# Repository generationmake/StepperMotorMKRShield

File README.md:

# StepperMotorMKRShield
StepperMotorMKRShield with Trinamic TMC5130A-TA drivers for two stepper motors compatible with Arduino MKR 

## PCB

### Top

### Bottom

## License

This hardware is licensed under the CERN OHL v. 1.2

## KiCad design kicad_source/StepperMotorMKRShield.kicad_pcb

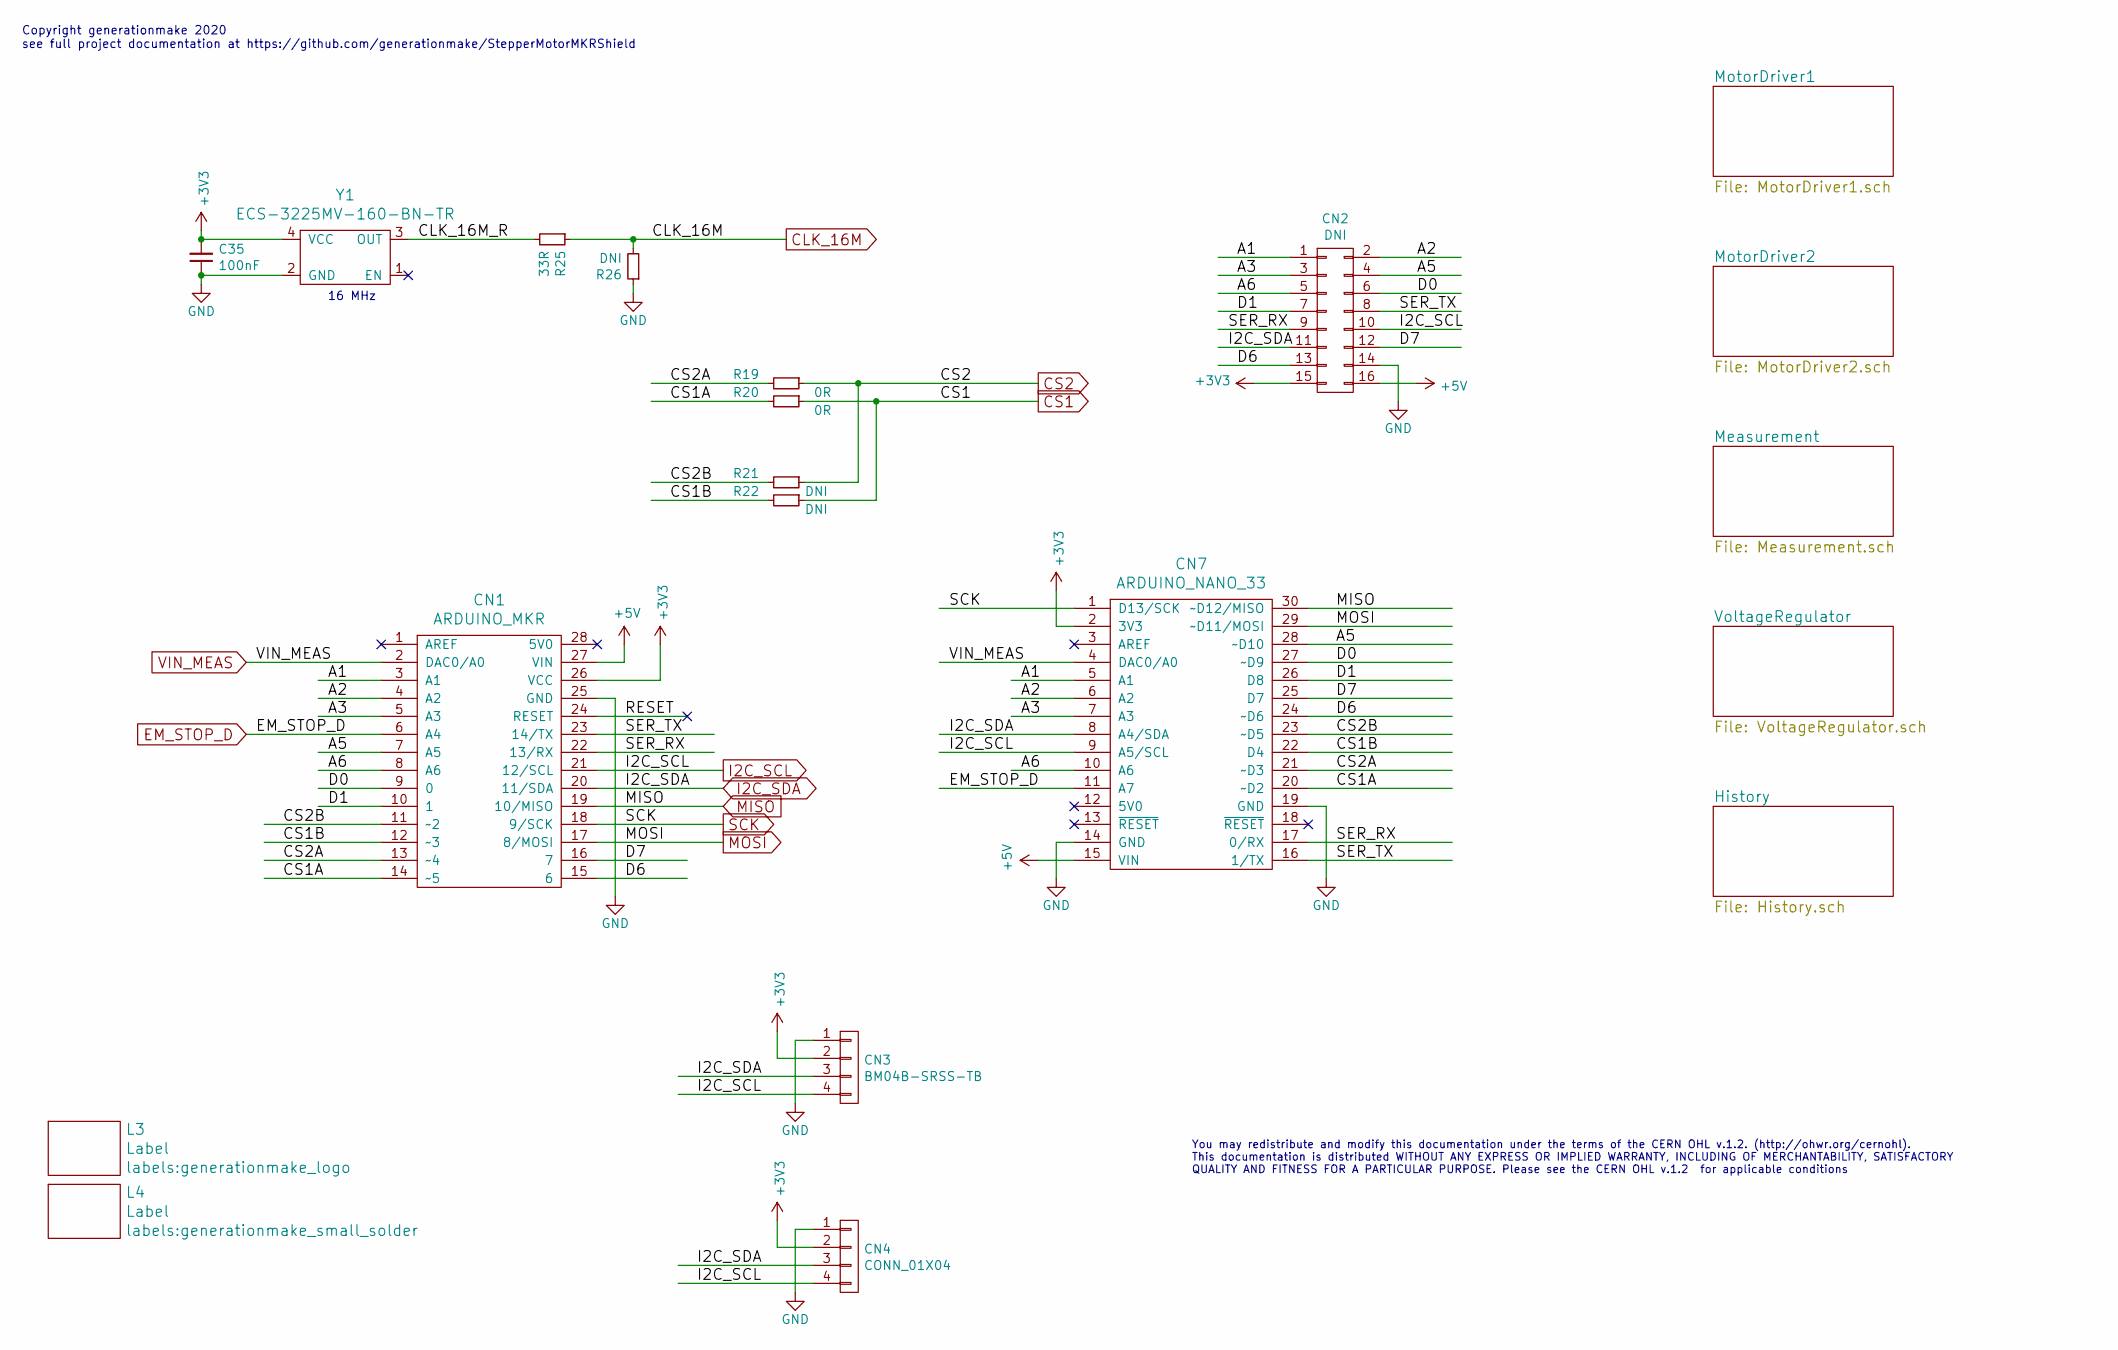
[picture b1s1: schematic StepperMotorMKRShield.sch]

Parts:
C35: 100nF; C_0603
CN1: ARDUINO_MKR; ARDUINO_MKR_BASEBOARD
CN2: DNI; Pin_Header_Straight_2x08
CN3: BM04B-SRSS-TB; Connectors_JST_BM04B-SRSS-TB
CN4: CONN_01X04; Pin_Header_Straight_1x04
CN7: ARDUINO_NANO_33
L3: Label; generationmake_logo
L4: Label; generationmake_small_solder
R19, R20: 0R; R_0603
R21, R22, R26: DNI; R_0603
R25: 33R; R_0603
Y1: ECS-3225MV-160-BN-TR; Crystal_SMD_3.2x2.5mm_4Pad

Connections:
+3V3: C35.2, CN1.26 (VCC), CN2.15, CN3.2, CN4.2, CN7.2 (3V3), Y1.4 (VCC); also elsewhere on the board
+5V: CN1.27 (VIN), CN2.16, CN7.15 (VIN); also elsewhere on the board
/A1: CN1.3 (A1), CN2.1, CN7.5 (A1)
/A2: CN1.4 (A2), CN2.2, CN7.6 (A2)
/A3: CN1.5 (A3), CN2.3, CN7.7 (A3)
/A5: CN1.7 (A5), CN2.4, CN7.28 (~~D10)
/A6: CN1.8 (A6), CN2.5, CN7.10 (A6)
/CLK_16M_R: R25.2, Y1.3 (OUT)
/CS1A: CN1.14 (~~5), CN7.20 (~~D2), R20.2
/CS1B: CN1.12 (~~3), CN7.22 (D4), R22.2
/CS2A: CN1.13 (~~4), CN7.21 (~~D3), R19.2
/CS2B: CN1.11 (~~2), CN7.23 (~~D5), R21.2
/D0: CN1.9 (0), CN2.6, CN7.27 (~~D9)
/D1: CN1.10 (1), CN2.7, CN7.26 (D8)
/D6: CN1.15 (6), CN2.13, CN7.24 (~~D6)
/D7: CN1.16 (7), CN2.12, CN7.25 (D7)
/SER_RX: CN1.22 (13/RX), CN2.9, CN7.17 (0/RX)
/SER_TX: CN1.23 (14/TX), CN2.8, CN7.16 (1/TX)
CLK_16M: R25.1, R26.2; also elsewhere on the board
CS1: R20.1, R22.1; also elsewhere on the board
CS2: R19.1, R21.1; also elsewhere on the board
EM_STOP_D: CN1.6 (A4), CN7.11 (A7); also elsewhere on the board
GND: C35.1, CN1.25 (GND), CN2.14, CN3.1, CN4.1, CN7.14 (GND), CN7.19 (GND), R26.1, Y1.2 (GND); also elsewhere on the board
I2C_SCL: CN1.21 (12/SCL), CN2.10, CN3.4, CN4.4, CN7.9 (A5/SCL); also elsewhere on the board
I2C_SDA: CN1.20 (11/SDA), CN2.11, CN3.3, CN4.3, CN7.8 (A4/SDA); also elsewhere on the board
MISO: CN1.19 (10/MISO), CN7.30 (~~D12/MISO); also elsewhere on the board
MOSI: CN1.17 (8/MOSI), CN7.29 (~~D11/MOSI); also elsewhere on the board
SCK: CN1.18 (9/SCK), CN7.1 (D13/SCK); also elsewhere on the board
VIN_MEAS: CN1.2 (DAC0/A0), CN7.4 (DAC0/A0); also elsewhere on the board

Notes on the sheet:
Copyright generationmake 2020 see full project documentation at https://github.com/generationmake/StepperMotorMKRShield
You may redistribute and modify this documentation under the terms of the CERN OHL v.1.2. (http://ohwr.org/cernohl). This documentation is distributed WITHOUT ANY EXPRESS OR IMPLIED WARRANTY, INCLUDING OF MERCHANTABILITY, SATISFACTORY QUALITY AND FITNESS FOR A PARTICULAR PURPOSE. Please see the CER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
16 MHz

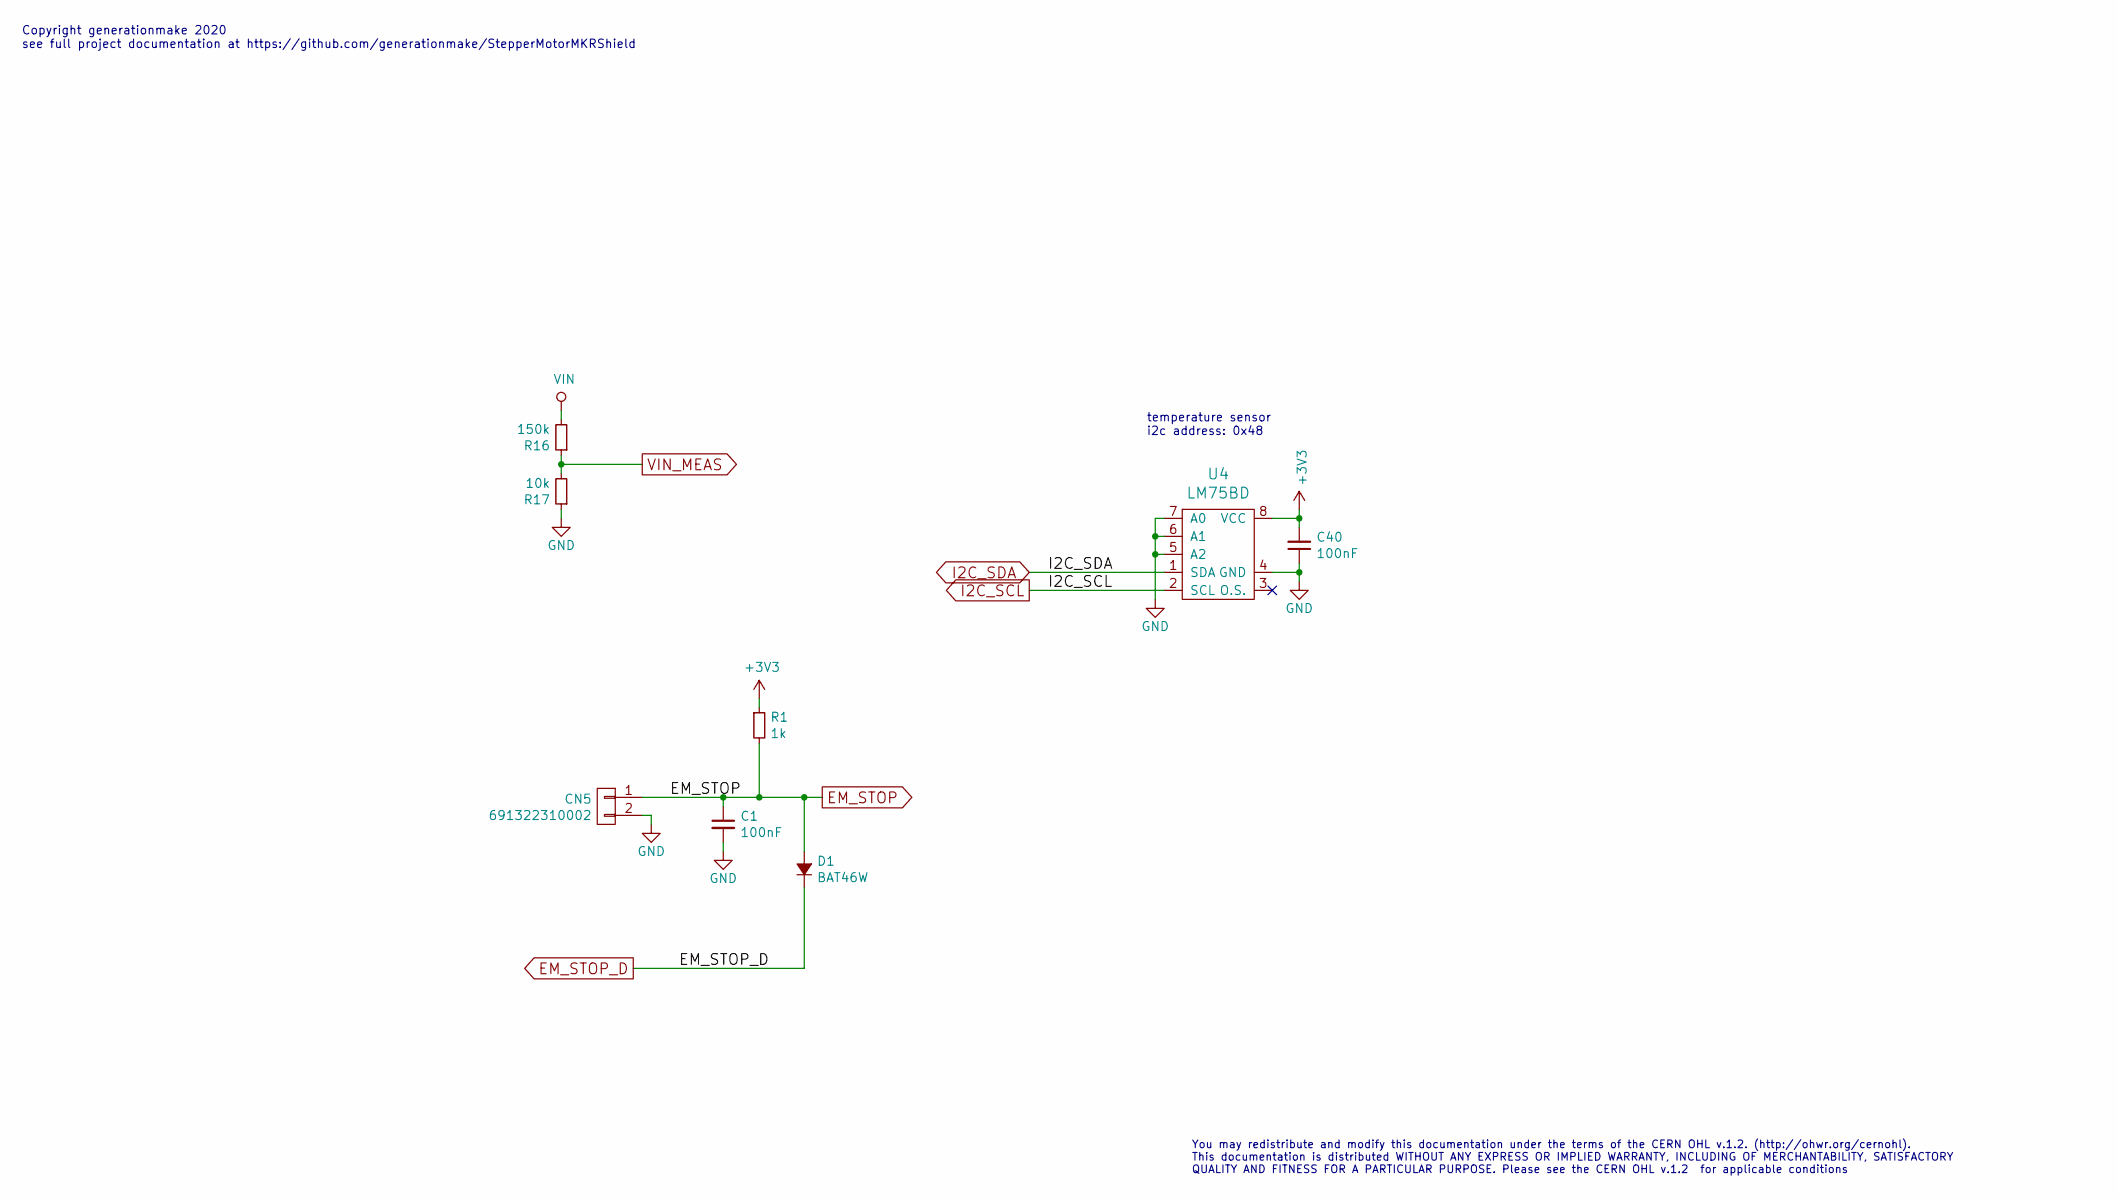
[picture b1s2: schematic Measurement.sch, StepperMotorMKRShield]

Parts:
C1, C40: 100nF; C_0603
CN5: 691322310002; WR-TBL_691322310002
D1: BAT46W; SOD-123
R1: 1k; R_0603
R16: 150k; R_0603
R17: 10k; R_0603
U4: LM75BD; SOIC-8_3.9x4.9mm_Pitch1.27mm

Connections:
+3V3: C40.2, R1.1, U4.8 (VCC); also elsewhere on the board
EM_STOP: C1.1, CN5.1, D1.2 (A), R1.2; also elsewhere on the board
EM_STOP_D: D1.1 (K); also elsewhere on the board
GND: C1.2, C40.1, CN5.2, R17.1, U4.4 (GND), U4.5 (A2), U4.6 (A1), U4.7 (A0); also elsewhere on the board
I2C_SCL: U4.2 (SCL); also elsewhere on the board
I2C_SDA: U4.1 (SDA); also elsewhere on the board
VIN: R16.2; also elsewhere on the board
VIN_MEAS: R16.1, R17.2; also elsewhere on the board

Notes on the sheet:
Copyright generationmake 2020 see full project documentation at https://github.com/generationmake/StepperMotorMKRShield
You may redistribute and modify this documentation under the terms of the CERN OHL v.1.2. (http://ohwr.org/cernohl). This documentation is distributed WITHOUT ANY EXPRESS OR IMPLIED WARRANTY, INCLUDING OF MERCHANTABILITY, SATISFACTORY QUALITY AND FITNESS FOR A PARTICULAR PURPOSE. Please see the CER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
temperature sensor i2c address: 0x48

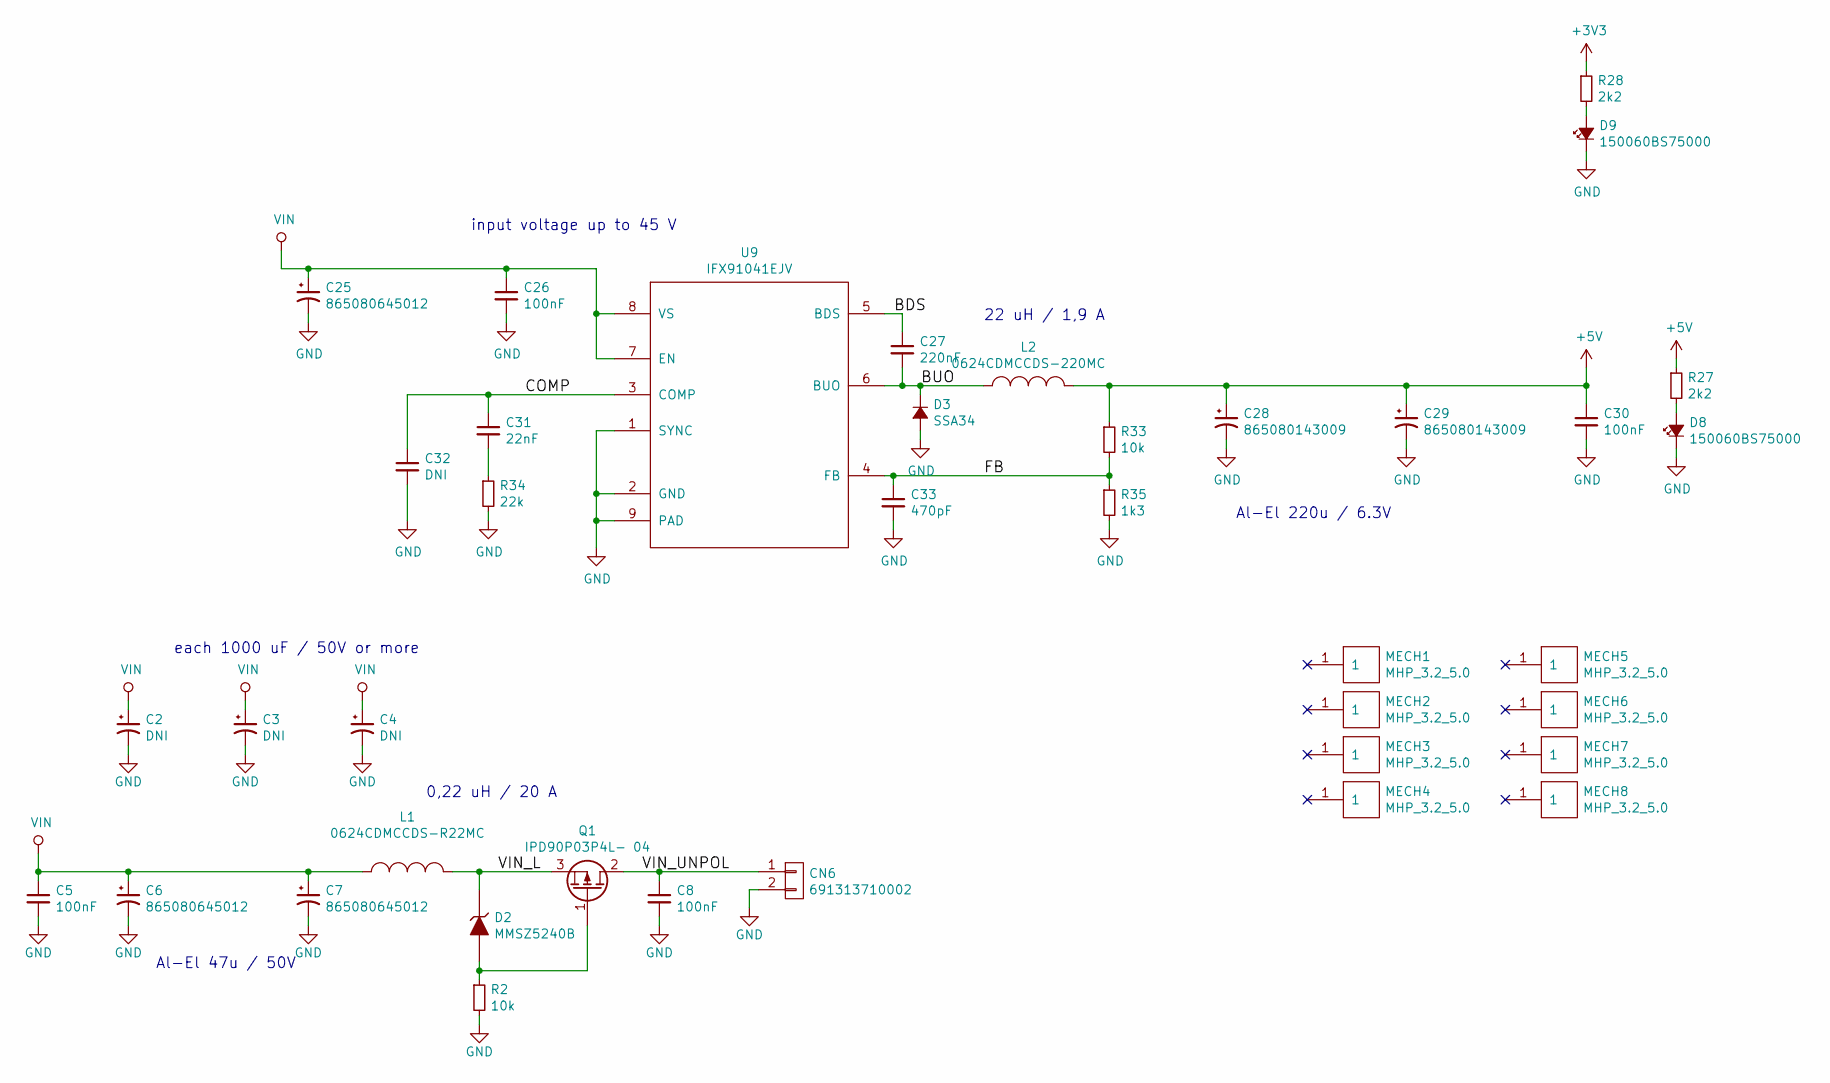
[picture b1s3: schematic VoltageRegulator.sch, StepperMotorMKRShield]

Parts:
C2, C3, C4: DNI; C_elec_THT_16x25_RM7.5
C5, C8, C26, C30: 100nF; C_0603
C6, C7, C25: 865080645012; c_elec_6.3x7.7
C27: 220nF; C_0603
C28, C29: 865080143009; c_elec_6.3x5.7
C31: 22nF; C_0603
C32: DNI; C_0603
C33: 470pF; C_0603
CN6: 691313710002; WR-TBL_691313710002
D2: MMSZ5240B; SOD-123
D3: SSA34; SMA_Standard
D8, D9: 150060BS75000; LED_0603
L1: 0624CDMCCDS-R22MC; Sumida-0624CDMCCDS
L2: 0624CDMCCDS-220MC; Sumida-0624CDMCCDS
MECH1, MECH2, MECH3, MECH4, MECH5, MECH6, MECH7, MECH8: MHP_3.2_5.0
Q1: IPD90P03P4L- 04; TO-252-2Lead
R2, R33: 10k; R_0603
R27, R28: 2k2; R_0603
R34: 22k; R_0603
R35: 1k3; R_0603
U9: IFX91041EJV; SOIC-8-1EP_3.9x4.9mm_Pitch1.27mm

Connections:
+3V3: R28.1; also elsewhere on the board
+5V: C28.1, C29.1, C30.1, L2.2, R27.1, R33.1; also elsewhere on the board
/VoltageRegulator/BDS: C27.1, U9.5 (BDS)
/VoltageRegulator/BUO: C27.2, D3.1 (K), L2.1, U9.6 (BUO)
/VoltageRegulator/COMP: C31.1, C32.1, U9.3 (COMP)
/VoltageRegulator/FB: C33.1, R33.2, R35.1, U9.4 (FB)
/VoltageRegulator/VIN_L: D2.1 (K), L1.2, Q1.3 (S)
/VoltageRegulator/VIN_UNPOL: C8.1, CN6.1, Q1.2 (D)
GND: C2.2, C3.2, C4.2, C5.2, C6.2, C7.2, C8.2, C25.2, C26.2, C28.2, C29.2, C30.2, C32.2, C33.2, CN6.2, D3.2 (A), D8.1 (K), D9.1 (K), R2.2, R34.2, R35.2, U9.1 (SYNC), U9.2 (GND), U9.9 (PAD); also elsewhere on the board
unnamed: C31.2, R34.1
unnamed: D2.2 (A), Q1.1 (G), R2.1
unnamed: D8.2 (A), R27.2
unnamed: D9.2 (A), R28.2
VIN: C2.1, C3.1, C4.1, C5.1, C6.1, C7.1, C25.1, C26.1, L1.1, U9.7 (EN), U9.8 (VS); also elsewhere on the board

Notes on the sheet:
input voltage up to 45 V
0,22 uH / 20 A
22 uH / 1,9 A
each 1000 uF / 50V or more
Al-El 47u / 50V
Al-El 220u / 6.3V

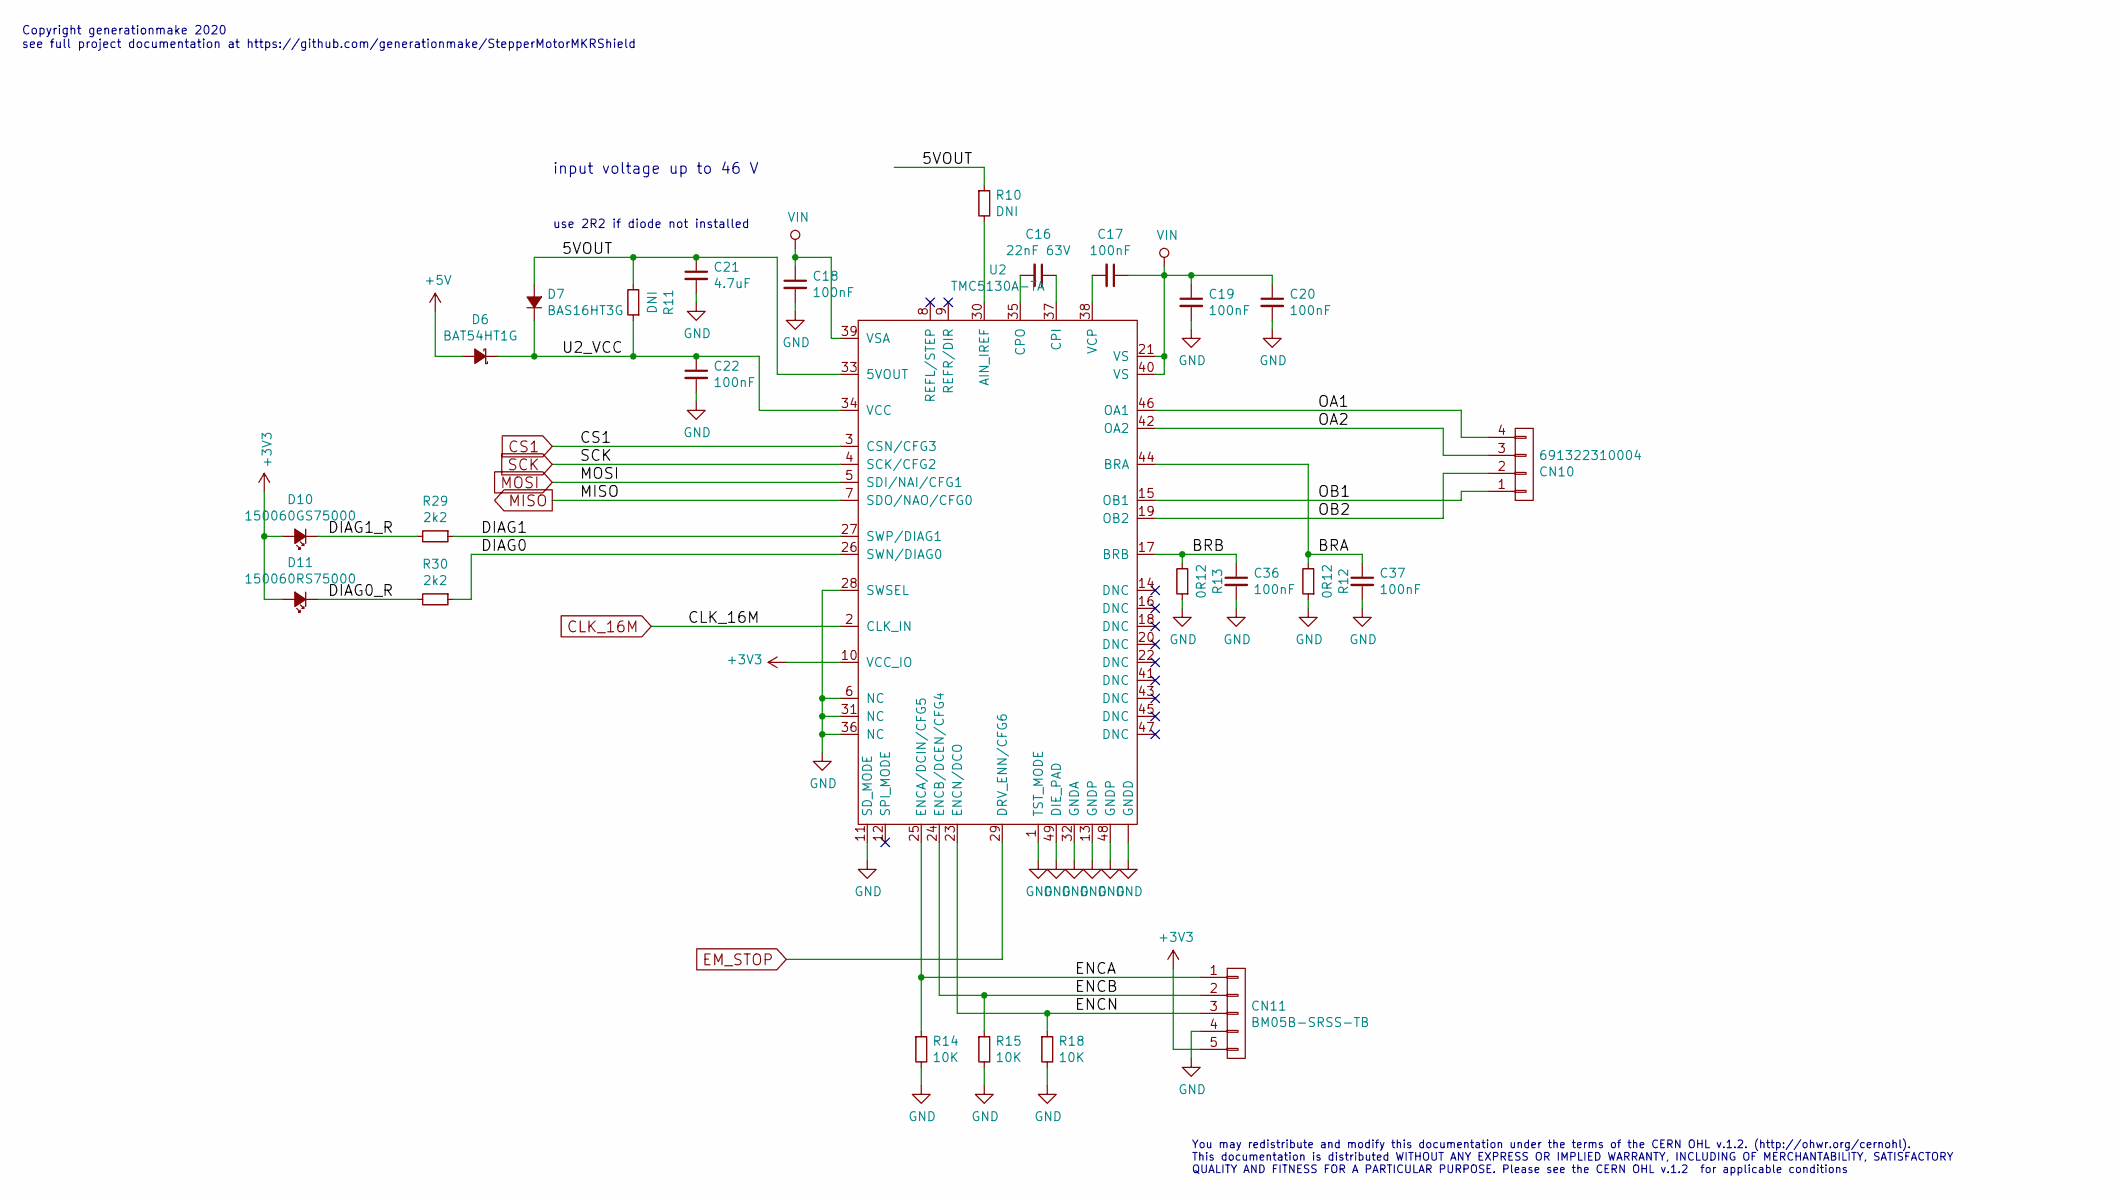
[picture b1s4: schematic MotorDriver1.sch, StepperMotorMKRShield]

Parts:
C16: 22nF 63V; C_0603
C17, C18, C19, C20, C22, C36, C37: 100nF; C_0603
C21: 4.7uF; C_0603
CN10: 691322310004; WR-TBL_691322310004
CN11: BM05B-SRSS-TB; Connectors_JST_BM05B-SRSS-TB
D6: BAT54HT1G; SOD-323
D7: BAS16HT3G; SOD-323
D10: 150060GS75000; LED_0603
D11: 150060RS75000; LED_0603
R10, R11: DNI; R_0603
R12, R13: 0R12; R_0805
R14, R15, R18: 10K; R_0603
R29, R30: 2k2; R_0603
U2: TMC5130A-TA; TQFP-48-1EP_7x7mm_Pitch0.5mm

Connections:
+3V3: CN11.5, D10.2 (A), D11.2 (A), U2.10 (VCC_IO); also elsewhere on the board
+5V: D6.2 (A); also elsewhere on the board
/MotorDriver1/5VOUT: C21.1, D7.2 (A), R10.1, R11.2, U2.33 (5VOUT)
/MotorDriver1/BRA: C37.1, R12.2, U2.44 (BRA)
/MotorDriver1/BRB: C36.1, R13.2, U2.17 (BRB)
/MotorDriver1/DIAG0: R30.1, U2.26 (SWN/DIAG0)
/MotorDriver1/DIAG0_R: D11.1 (K), R30.2
/MotorDriver1/DIAG1: R29.1, U2.27 (SWP/DIAG1)
/MotorDriver1/DIAG1_R: D10.1 (K), R29.2
/MotorDriver1/ENCA: CN11.1, R14.1, U2.25 (ENCA/DCIN/CFG5)
/MotorDriver1/ENCB: CN11.2, R15.1, U2.24 (ENCB/DCEN/CFG4)
/MotorDriver1/ENCN: CN11.3, R18.1, U2.23 (ENCN/DCO)
/MotorDriver1/OA1: CN10.4, U2.46 (OA1)
/MotorDriver1/OA2: CN10.3, U2.42 (OA2)
/MotorDriver1/OB1: CN10.1, U2.15 (OB1)
/MotorDriver1/OB2: CN10.2, U2.19 (OB2)
/MotorDriver1/U2_VCC: C22.1, D6.1 (K), D7.1 (K), R11.1, U2.34 (VCC)
CLK_16M: U2.2 (CLK_IN); also elsewhere on the board
CS1: U2.3 (CSN/CFG3); also elsewhere on the board
EM_STOP: U2.29 (DRV_ENN/CFG6); also elsewhere on the board
GND: C18.2, C19.2, C20.2, C21.2, C22.2, C36.2, C37.2, CN11.4, R12.1, R13.1, R14.2, R15.2, R18.2, U2.1 (TST_MODE), U2.6 (NC), U2.11 (SD_MODE), U2.13 (GNDP), U2.28 (SWSEL), U2.31 (NC), U2.32 (GNDA), U2.36 (NC), U2.48 (GNDP), U2.49 (DIE_PAD), U2.~ (GNDD); also elsewhere on the board
MISO: U2.7 (SDO/NAO/CFG0); also elsewhere on the board
MOSI: U2.5 (SDI/NAI/CFG1); also elsewhere on the board
unnamed: C16.1, U2.37 (CPI)
unnamed: C16.2, U2.35 (CPO)
unnamed: C17.2, U2.38 (VCP)
unnamed: R10.2, U2.30 (AIN_IREF)
SCK: U2.4 (SCK/CFG2); also elsewhere on the board
VIN: C17.1, C18.1, C19.1, C20.1, U2.21 (VS), U2.39 (VSA), U2.40 (VS); also elsewhere on the board

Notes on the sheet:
Copyright generationmake 2020 see full project documentation at https://github.com/generationmake/StepperMotorMKRShield
You may redistribute and modify this documentation under the terms of the CERN OHL v.1.2. (http://ohwr.org/cernohl). This documentation is distributed WITHOUT ANY EXPRESS OR IMPLIED WARRANTY, INCLUDING OF MERCHANTABILITY, SATISFACTORY QUALITY AND FITNESS FOR A PARTICULAR PURPOSE. Please see the CER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
use 2R2 if diode not installed
input voltage up to 46 V

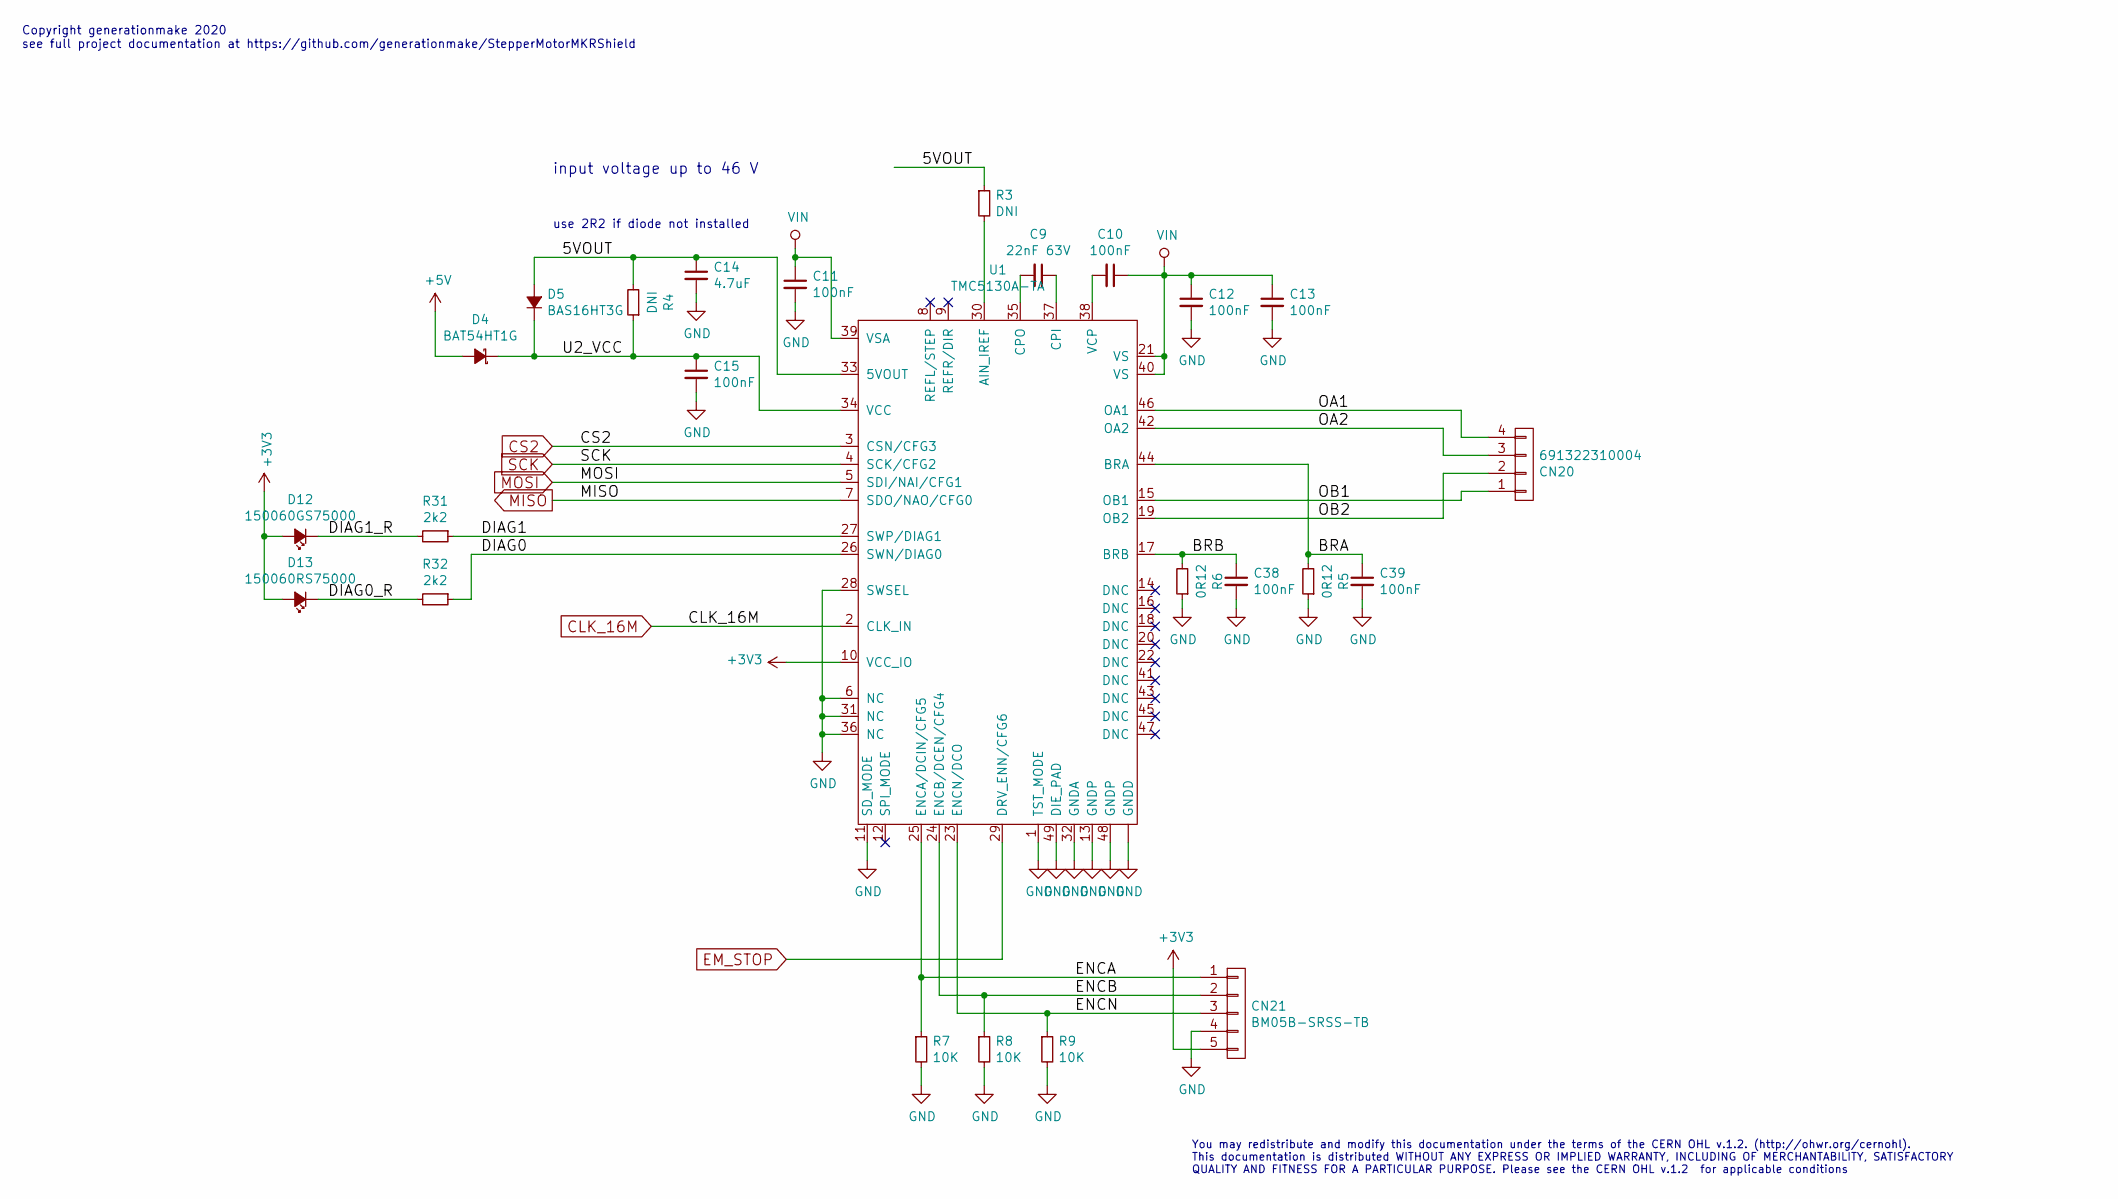
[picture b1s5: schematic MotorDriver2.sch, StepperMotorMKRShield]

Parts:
C9: 22nF 63V; C_0603
C10, C11, C12, C13, C15, C38, C39: 100nF; C_0603
C14: 4.7uF; C_0603
CN20: 691322310004; WR-TBL_691322310004
CN21: BM05B-SRSS-TB; Connectors_JST_BM05B-SRSS-TB
D4: BAT54HT1G; SOD-323
D5: BAS16HT3G; SOD-323
D12: 150060GS75000; LED_0603
D13: 150060RS75000; LED_0603
R3, R4: DNI; R_0603
R5, R6: 0R12; R_0805
R7, R8, R9: 10K; R_0603
R31, R32: 2k2; R_0603
U1: TMC5130A-TA; TQFP-48-1EP_7x7mm_Pitch0.5mm

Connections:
+3V3: CN21.5, D12.2 (A), D13.2 (A), U1.10 (VCC_IO); also elsewhere on the board
+5V: D4.2 (A); also elsewhere on the board
/MotorDriver2/5VOUT: C14.1, D5.2 (A), R3.1, R4.2, U1.33 (5VOUT)
/MotorDriver2/BRA: C39.1, R5.2, U1.44 (BRA)
/MotorDriver2/BRB: C38.1, R6.2, U1.17 (BRB)
/MotorDriver2/DIAG0: R32.1, U1.26 (SWN/DIAG0)
/MotorDriver2/DIAG0_R: D13.1 (K), R32.2
/MotorDriver2/DIAG1: R31.1, U1.27 (SWP/DIAG1)
/MotorDriver2/DIAG1_R: D12.1 (K), R31.2
/MotorDriver2/ENCA: CN21.1, R7.1, U1.25 (ENCA/DCIN/CFG5)
/MotorDriver2/ENCB: CN21.2, R8.1, U1.24 (ENCB/DCEN/CFG4)
/MotorDriver2/ENCN: CN21.3, R9.1, U1.23 (ENCN/DCO)
/MotorDriver2/OA1: CN20.4, U1.46 (OA1)
/MotorDriver2/OA2: CN20.3, U1.42 (OA2)
/MotorDriver2/OB1: CN20.1, U1.15 (OB1)
/MotorDriver2/OB2: CN20.2, U1.19 (OB2)
/MotorDriver2/U2_VCC: C15.1, D4.1 (K), D5.1 (K), R4.1, U1.34 (VCC)
CLK_16M: U1.2 (CLK_IN); also elsewhere on the board
CS2: U1.3 (CSN/CFG3); also elsewhere on the board
EM_STOP: U1.29 (DRV_ENN/CFG6); also elsewhere on the board
GND: C11.2, C12.2, C13.2, C14.2, C15.2, C38.2, C39.2, CN21.4, R5.1, R6.1, R7.2, R8.2, R9.2, U1.1 (TST_MODE), U1.6 (NC), U1.11 (SD_MODE), U1.13 (GNDP), U1.28 (SWSEL), U1.31 (NC), U1.32 (GNDA), U1.36 (NC), U1.48 (GNDP), U1.49 (DIE_PAD), U1.~ (GNDD); also elsewhere on the board
MISO: U1.7 (SDO/NAO/CFG0); also elsewhere on the board
MOSI: U1.5 (SDI/NAI/CFG1); also elsewhere on the board
unnamed: C9.1, U1.37 (CPI)
unnamed: C9.2, U1.35 (CPO)
unnamed: C10.2, U1.38 (VCP)
unnamed: R3.2, U1.30 (AIN_IREF)
SCK: U1.4 (SCK/CFG2); also elsewhere on the board
VIN: C10.1, C11.1, C12.1, C13.1, U1.21 (VS), U1.39 (VSA), U1.40 (VS); also elsewhere on the board

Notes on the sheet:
Copyright generationmake 2020 see full project documentation at https://github.com/generationmake/StepperMotorMKRShield
You may redistribute and modify this documentation under the terms of the CERN OHL v.1.2. (http://ohwr.org/cernohl). This documentation is distributed WITHOUT ANY EXPRESS OR IMPLIED WARRANTY, INCLUDING OF MERCHANTABILITY, SATISFACTORY QUALITY AND FITNESS FOR A PARTICULAR PURPOSE. Please see the CER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
use 2R2 if diode not installed
input voltage up to 46 V

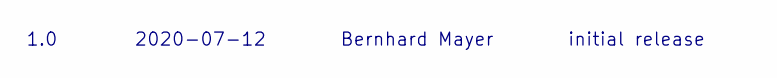
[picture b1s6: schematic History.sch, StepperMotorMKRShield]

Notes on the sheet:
1.0
2020-07-12
Bernhard Mayer
initial release

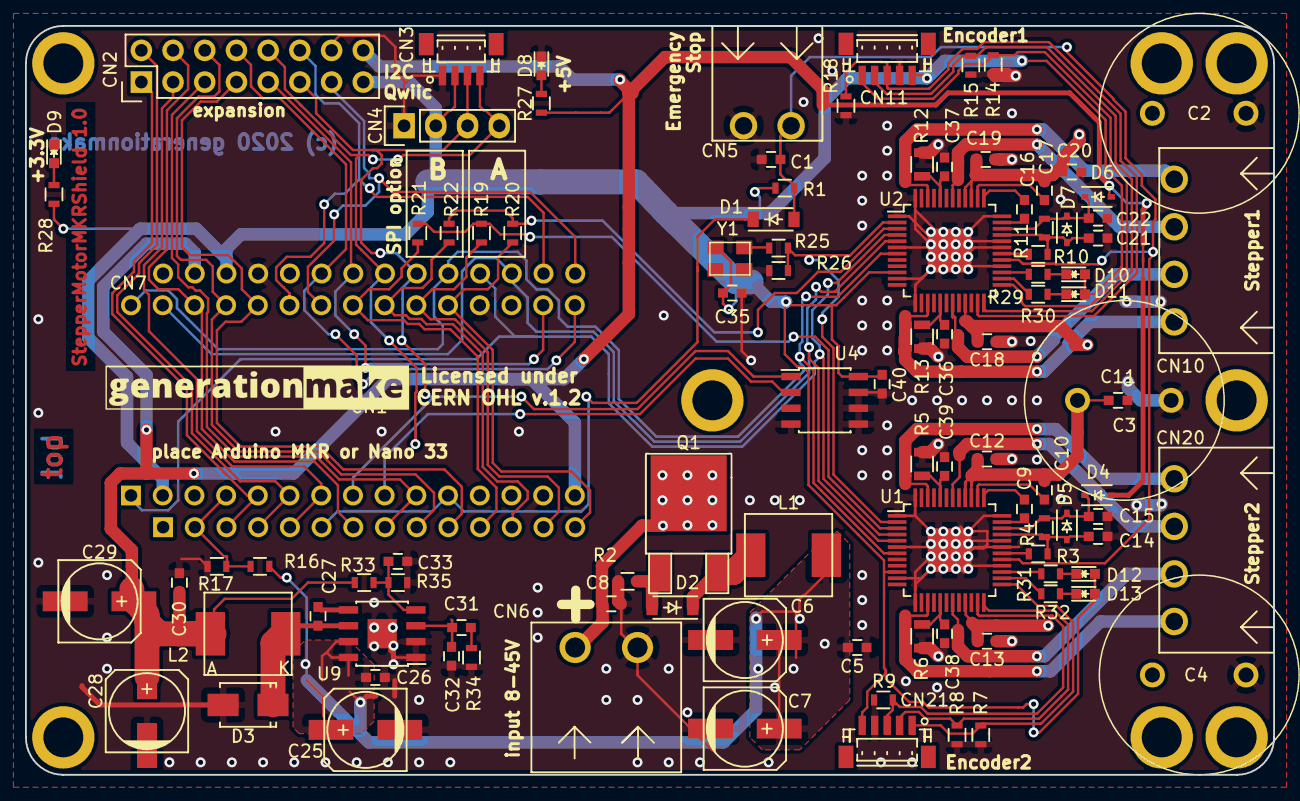
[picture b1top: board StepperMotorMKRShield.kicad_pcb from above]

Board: 2 copper layers, 100.0 x 60.0 mm, 112 parts (0 on the bottom side), 79 nets.

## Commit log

2019-12-31 added kicad source
2019-12-31 generated pdf files
2019-12-31 added license information
2019-12-31 added documentation images
2020-01-01 added mounting instructions
2020-04-16 added most missing 3d models, changed mounting holes to parts and generated step model
2020-07-03 fix cache before start of new version
2020-07-03 added external supply for +5V for TMC5130
2020-07-03 added clock generator as common clock for both stepper drivers
2020-07-04 added leds and decoupling capacitors
2020-07-04 changed type of encoder connector
2020-07-05 added temperature sensor LM75
2020-07-06 updated layout
2020-07-07 update layout
2020-07-07 added expansion connector, updated layout
2020-07-07 added pdf schematic and renderings
2020-07-08 updated part numbers
2020-07-11 corrected position of mounting holes for heat spreader, added information on input voltage
2020-07-11 changed L1 and L2 to Sumida 0624CDMCCDS for better availability
2020-07-11 corrected order numbers of capacitors
2020-07-11 renamed all images
2020-07-11 updated all images
2020-07-11 updated pdf files
2020-07-11 updated changes file
2020-07-11 updated step file (3d model)
2020-07-11 updated links in readme
2020-07-11 renamed all files to new project name
2020-07-11 added CN1 from adafruit feather to arduino MKR
2020-07-11 removed regulator for 5V external
2020-07-11 corrected links and titles, generated schematic pdf and net list
2020-07-12 updated images
2020-07-12 added Arduino Nano 33 header in schematic
2020-07-12 replaced tantal capacitors with aluminium-electronlytic capacitors with higher voltage to allow up to 45 V on input
2020-07-13 generated pdf schematic

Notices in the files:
kicad_source/History.sch:
This documentation describes Open Hardware and is licensed under the CERN OHL v. 1.2.
kicad_source/StepperMotorMKRShield.kicad_pcb:
(c) 2020 generationmake
